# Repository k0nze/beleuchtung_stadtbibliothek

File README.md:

# Beleuchtung der LEGO Stadtbibliothek Stuttgart

## Platine
KiCad Projekt:
[beleuchtung_stadtbibliothek.pro](./kicad/beleuchtung_stadtbibliothek.pro)

Pin-Belegung `CON1`:

 * 1 => `VCC`
 * 2 => `GND`
 * 3 => `CLK`
 * 4 => Clear für für Schieberegister
 * 5 => Data-Input für Schieberegister 
 * 6 => Enable für LED-Treiber 

### Schaltplan
[beleuchtung_stadtbibliothek.sch](./kicad/beleuchtung_stadtbibliothek.sch)

### Layout/PCB
[beleuchtung_stadtbibliothek.kicad_pcb](./kicad/beleuchtung_stadtbibliothek.kicad_pcb)

### Gerber Dateien für Seeedstudio
[kicad/gerber](./kicad/gerber)

### Bauelemente (für 10 Platinen)
Reichelt:

 * 10x [Stiftleisten 2,54 mm, 2X03, gewinkelt](https://www.reichelt.de/Stiftleisten/MPE-088-2-006/3/index.html?ACTION=3&LA=2&ARTICLE=119904&GROUPID=7434&artnr=MPE+088-2-006&SEARCH=%252A)
 * 15x [50pol. Stiftleiste, gewinkelt, RM 2,54](https://www.reichelt.de/Stiftleisten/SL-1X50W-2-54/3/index.html?ACTION=3&LA=2&ARTICLE=19509&GROUPID=7434&artnr=SL+1X50W+2%2C54&SEARCH=%252A)
 * 50x [SMD HC 164](https://www.reichelt.de/ICs-74HC-SMD/SMD-HC-164/3/index.html?ACTION=3&LA=2&ARTICLE=18650&GROUPID=2931&artnr=SMD+HC+164&SEARCH=%252A)
 * 50x [SMD HC 244](https://www.reichelt.de/ICs-74HC-SMD/SMD-HC-244/3/index.html?ACTION=3&LA=2&ARTICLE=18663&GROUPID=2931&artnr=SMD+HC+244&SEARCH=%252A)
 * 2x [CR 44](https://www.reichelt.de/Flussmittel-Loetpasten/CR-44/3/index.html?ACTION=3&LA=2&ARTICLE=6833&GROUPID=4132&artnr=CR+44&SEARCH=%252A)
 * (3-5)x [GS25E05-P1J](https://www.reichelt.de/Festspannungsnetzteile/GS25E05-P1J/3/index.html?ACTION=3&LA=2&ARTICLE=161618&GROUPID=4946&artnr=GS25E05-P1J&SEARCH=%252A)
 * (3-5)x [DELOCK 65524](https://www.reichelt.de/Hohlstecker/DELOCK-65524/3/index.html?ACTION=3&LA=2&ARTICLE=143219&GROUPID=7488&artnr=DELOCK+65524&SEARCH=%252A)
 * 1x [EL 6-FACH MS-LG](https://www.reichelt.de/Steckdosenleiste-allgemein/EL-6-FACH-MS-LG/3/index.html?ACTION=3&LA=446&ARTICLE=34994&GROUPID=4280&artnr=EL+6-FACH+MS-LG&SEARCH=mehrfachsteckdose)
 * 360x [1/4W 5%](https://www.reichelt.de/1-4W-5-/2/index.html?ACTION=2&LA=2&GROUPID=3061)

eBay:

 * 500x [3mm LED weiß](http://www.ebay.de/itm/Transparente-High-Quality-LEDs-Leucht-Dioden-in-verschiedenen-Grosen-und-Farben-/171370401875?var=&hash=item27e678d053:m:myDHtgaZcdvr4vHanhSXiCA)
 * 18x [20cm Dupont Draht 40x](http://www.ebay.de/itm/40x-Dupont-Draht-Rainbow-Color-Jumper-Kabel-Buchse-Buchse-20cm-/351673233241?hash=item51e15baf59:g:O0cAAOxyaTxTRRo8)

Bricklink:

 * 360x [4070, white](https://www.bricklink.com/v2/catalog/catalogitem.page?P=4070#T=S&C=1&O={"color":1})

## Steuerung
Die Steuerung wird derzeit durch einen Arduino Mega 2560 übernommen. Der Anschluss der Steuerleitungen für die Platinen ist in [demo0.ino](./src/demo0/demo0.ino) dokumentiert. In [demo0.ino](./src/demo0/demo0.ino) werden alle LEDs eingeschaltet.

### Verdrahtung

* `VCC`: orange
* `GND`: blau/schwarz
* `CLK`: violett/orange
* reset: weiß
* data: gelb/grün
* driver: grau/braun

### Fertiges Modell

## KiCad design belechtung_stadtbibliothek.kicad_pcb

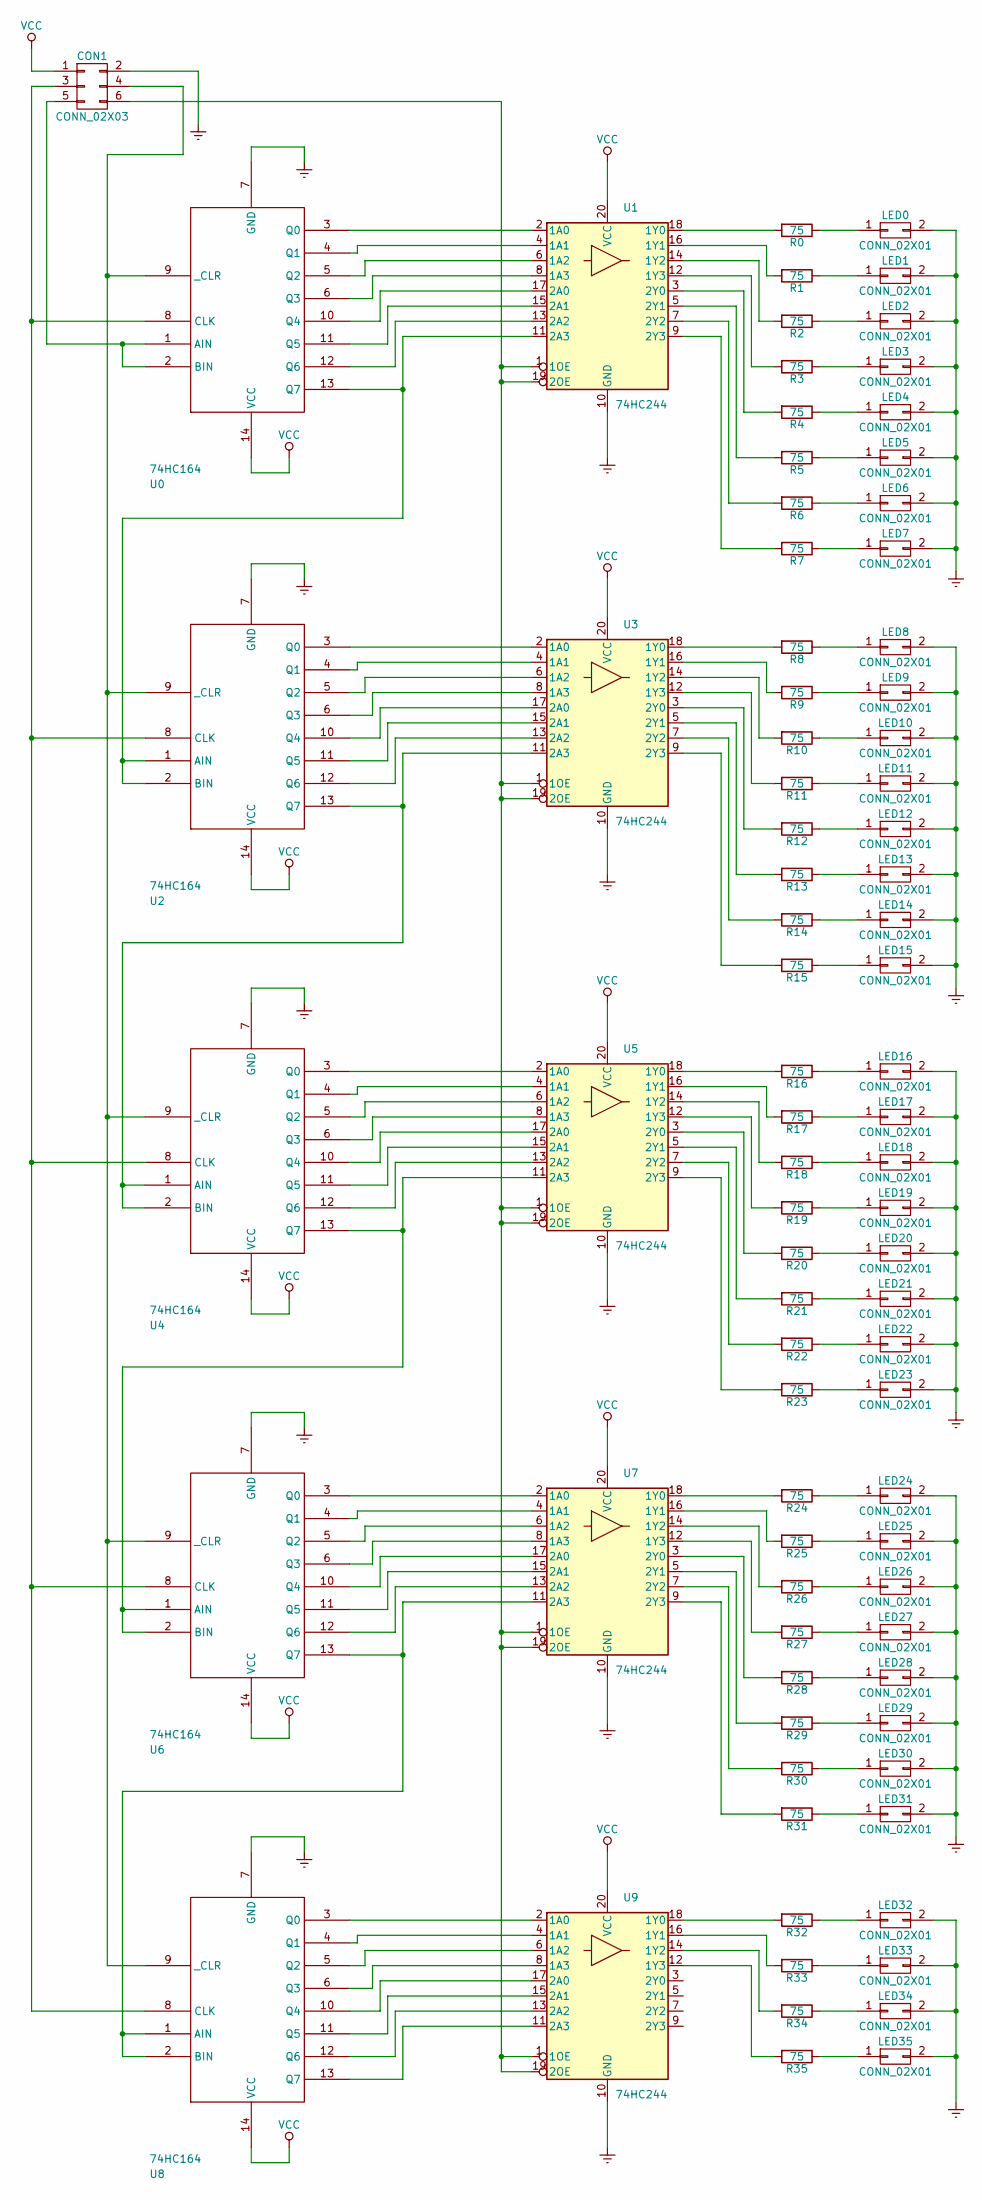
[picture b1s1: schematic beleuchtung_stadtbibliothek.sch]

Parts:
CON1: CONN_02X03; Pin_Header_Straight_2x03_Pitch2.54mm
LED0, LED1, LED2, LED3, LED4, LED5, LED6, LED7, LED8, LED9, LED10, LED11, LED12, LED13, LED14, LED15, LED16, LED17, LED18, LED19, LED20, LED21, LED22, LED23, LED24, LED25, LED26, LED27, LED28, LED29, LED30, LED31, LED32, LED33, LED34, LED35: CONN_02X01; Pin_Header_Angled_1x02_Pitch2.54mm
R0, R1, R2, R3, R4, R5, R6, R7, R8, R9, R10, R11, R12, R13, R14, R15, R16, R17, R18, R19, R20, R21, R22, R23, R24, R25, R26, R27, R28, R29, R30, R31, R32, R33, R34, R35: 75; R_Axial_DIN0204_L3.6mm_D1.6mm_P2.54mm_Vertical
U0, U2, U4, U6, U8: 74HC164; DIP-14_W7.62mm_LongPads
U1, U3, U5, U7, U9: 74HC244; DIP-20_W7.62mm_LongPads

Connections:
Earth: CON1.2, LED0.2, LED1.2, LED2.2, LED3.2, LED4.2, LED5.2, LED6.2, LED7.2, LED8.2, LED9.2, LED10.2, LED11.2, LED12.2, LED13.2, LED14.2, LED15.2, LED16.2, LED17.2, LED18.2, LED19.2, LED20.2, LED21.2, LED22.2, LED23.2, LED24.2, LED25.2, LED26.2, LED27.2, LED28.2, LED29.2, LED30.2, LED31.2, LED32.2, LED33.2, LED34.2, LED35.2, U0.7 (GND), U1.10 (GND), U2.7 (GND), U3.10 (GND), U4.7 (GND), U5.10 (GND), U6.7 (GND), U7.10 (GND), U8.7 (GND), U9.10 (GND)
unnamed: CON1.3, U0.8 (CLK), U2.8 (CLK), U4.8 (CLK), U6.8 (CLK), U8.8 (CLK)
unnamed: CON1.4, U0.9 (_CLR), U2.9 (_CLR), U4.9 (_CLR), U6.9 (_CLR), U8.9 (_CLR)
unnamed: CON1.5, U0.1 (AIN), U0.2 (BIN)
unnamed: CON1.6, U1.1 (1OE), U1.19 (2OE), U3.1 (1OE), U3.19 (2OE), U5.1 (1OE), U5.19 (2OE), U7.1 (1OE), U7.19 (2OE), U9.1 (1OE), U9.19 (2OE)
unnamed: LED0.1, R0.1
unnamed: LED1.1, R1.1
unnamed: LED2.1, R2.1
unnamed: LED3.1, R3.1
unnamed: LED4.1, R4.1
unnamed: LED5.1, R5.1
unnamed: LED6.1, R6.1
unnamed: LED7.1, R7.1
unnamed: LED8.1, R8.1
unnamed: LED9.1, R9.1
unnamed: LED10.1, R10.1
unnamed: LED11.1, R11.1
unnamed: LED12.1, R12.1
unnamed: LED13.1, R13.1
unnamed: LED14.1, R14.1
unnamed: LED15.1, R15.1
unnamed: LED16.1, R16.1
unnamed: LED17.1, R17.1
unnamed: LED18.1, R18.1
unnamed: LED19.1, R19.1
unnamed: LED20.1, R20.1
unnamed: LED21.1, R21.1
unnamed: LED22.1, R22.1
unnamed: LED23.1, R23.1
unnamed: LED24.1, R24.1
unnamed: LED25.1, R25.1
unnamed: LED26.1, R26.1
unnamed: LED27.1, R27.1
unnamed: LED28.1, R28.1
unnamed: LED29.1, R29.1
unnamed: LED30.1, R30.1
unnamed: LED31.1, R31.1
unnamed: LED32.1, R32.1
unnamed: LED33.1, R33.1
unnamed: LED34.1, R34.1
unnamed: LED35.1, R35.1
unnamed: R0.2, U1.18 (1Y0)
unnamed: R1.2, U1.16 (1Y1)
unnamed: R2.2, U1.14 (1Y2)
unnamed: R3.2, U1.12 (1Y3)
unnamed: R4.2, U1.3 (2Y0)
unnamed: R5.2, U1.5 (2Y1)
unnamed: R6.2, U1.7 (2Y2)
unnamed: R7.2, U1.9 (2Y3)
unnamed: R8.2, U3.18 (1Y0)
unnamed: R9.2, U3.16 (1Y1)
unnamed: R10.2, U3.14 (1Y2)
unnamed: R11.2, U3.12 (1Y3)
unnamed: R12.2, U3.3 (2Y0)
unnamed: R13.2, U3.5 (2Y1)
unnamed: R14.2, U3.7 (2Y2)
unnamed: R15.2, U3.9 (2Y3)
unnamed: R16.2, U5.18 (1Y0)
unnamed: R17.2, U5.16 (1Y1)
unnamed: R18.2, U5.14 (1Y2)
unnamed: R19.2, U5.12 (1Y3)
unnamed: R20.2, U5.3 (2Y0)
unnamed: R21.2, U5.5 (2Y1)
unnamed: R22.2, U5.7 (2Y2)
unnamed: R23.2, U5.9 (2Y3)
unnamed: R24.2, U7.18 (1Y0)
unnamed: R25.2, U7.16 (1Y1)
unnamed: R26.2, U7.14 (1Y2)
unnamed: R27.2, U7.12 (1Y3)
unnamed: R28.2, U7.3 (2Y0)
unnamed: R29.2, U7.5 (2Y1)
unnamed: R30.2, U7.7 (2Y2)
unnamed: R31.2, U7.9 (2Y3)
unnamed: R32.2, U9.18 (1Y0)
unnamed: R33.2, U9.16 (1Y1)
unnamed: R34.2, U9.14 (1Y2)
unnamed: R35.2, U9.12 (1Y3)
unnamed: U0.3 (Q0), U1.2 (1A0)
unnamed: U0.4 (Q1), U1.4 (1A1)
unnamed: U0.5 (Q2), U1.6 (1A2)
unnamed: U0.6 (Q3), U1.8 (1A3)
unnamed: U0.10 (Q4), U1.17 (2A0)
unnamed: U0.11 (Q5), U1.15 (2A1)
unnamed: U0.12 (Q6), U1.13 (2A2)
unnamed: U0.13 (Q7), U1.11 (2A3), U2.1 (AIN), U2.2 (BIN)
unnamed: U2.3 (Q0), U3.2 (1A0)
unnamed: U2.4 (Q1), U3.4 (1A1)
unnamed: U2.5 (Q2), U3.6 (1A2)
unnamed: U2.6 (Q3), U3.8 (1A3)
unnamed: U2.10 (Q4), U3.17 (2A0)
unnamed: U2.11 (Q5), U3.15 (2A1)
unnamed: U2.12 (Q6), U3.13 (2A2)
unnamed: U2.13 (Q7), U3.11 (2A3), U4.1 (AIN), U4.2 (BIN)
unnamed: U4.3 (Q0), U5.2 (1A0)
unnamed: U4.4 (Q1), U5.4 (1A1)
unnamed: U4.5 (Q2), U5.6 (1A2)
unnamed: U4.6 (Q3), U5.8 (1A3)
unnamed: U4.10 (Q4), U5.17 (2A0)
unnamed: U4.11 (Q5), U5.15 (2A1)
unnamed: U4.12 (Q6), U5.13 (2A2)
unnamed: U4.13 (Q7), U5.11 (2A3), U6.1 (AIN), U6.2 (BIN)
unnamed: U6.3 (Q0), U7.2 (1A0)
unnamed: U6.4 (Q1), U7.4 (1A1)
unnamed: U6.5 (Q2), U7.6 (1A2)
unnamed: U6.6 (Q3), U7.8 (1A3)
unnamed: U6.10 (Q4), U7.17 (2A0)
unnamed: U6.11 (Q5), U7.15 (2A1)
unnamed: U6.12 (Q6), U7.13 (2A2)
unnamed: U6.13 (Q7), U7.11 (2A3), U8.1 (AIN), U8.2 (BIN)
unnamed: U8.3 (Q0), U9.2 (1A0)
unnamed: U8.4 (Q1), U9.4 (1A1)
unnamed: U8.5 (Q2), U9.6 (1A2)
unnamed: U8.6 (Q3), U9.8 (1A3)
unnamed: U8.10 (Q4), U9.17 (2A0)
unnamed: U8.11 (Q5), U9.15 (2A1)
unnamed: U8.12 (Q6), U9.13 (2A2)
unnamed: U8.13 (Q7), U9.11 (2A3)
VCC: CON1.1, U0.14 (VCC), U1.20 (VCC), U2.14 (VCC), U3.20 (VCC), U4.14 (VCC), U5.20 (VCC), U6.14 (VCC), U7.20 (VCC), U8.14 (VCC), U9.20 (VCC)

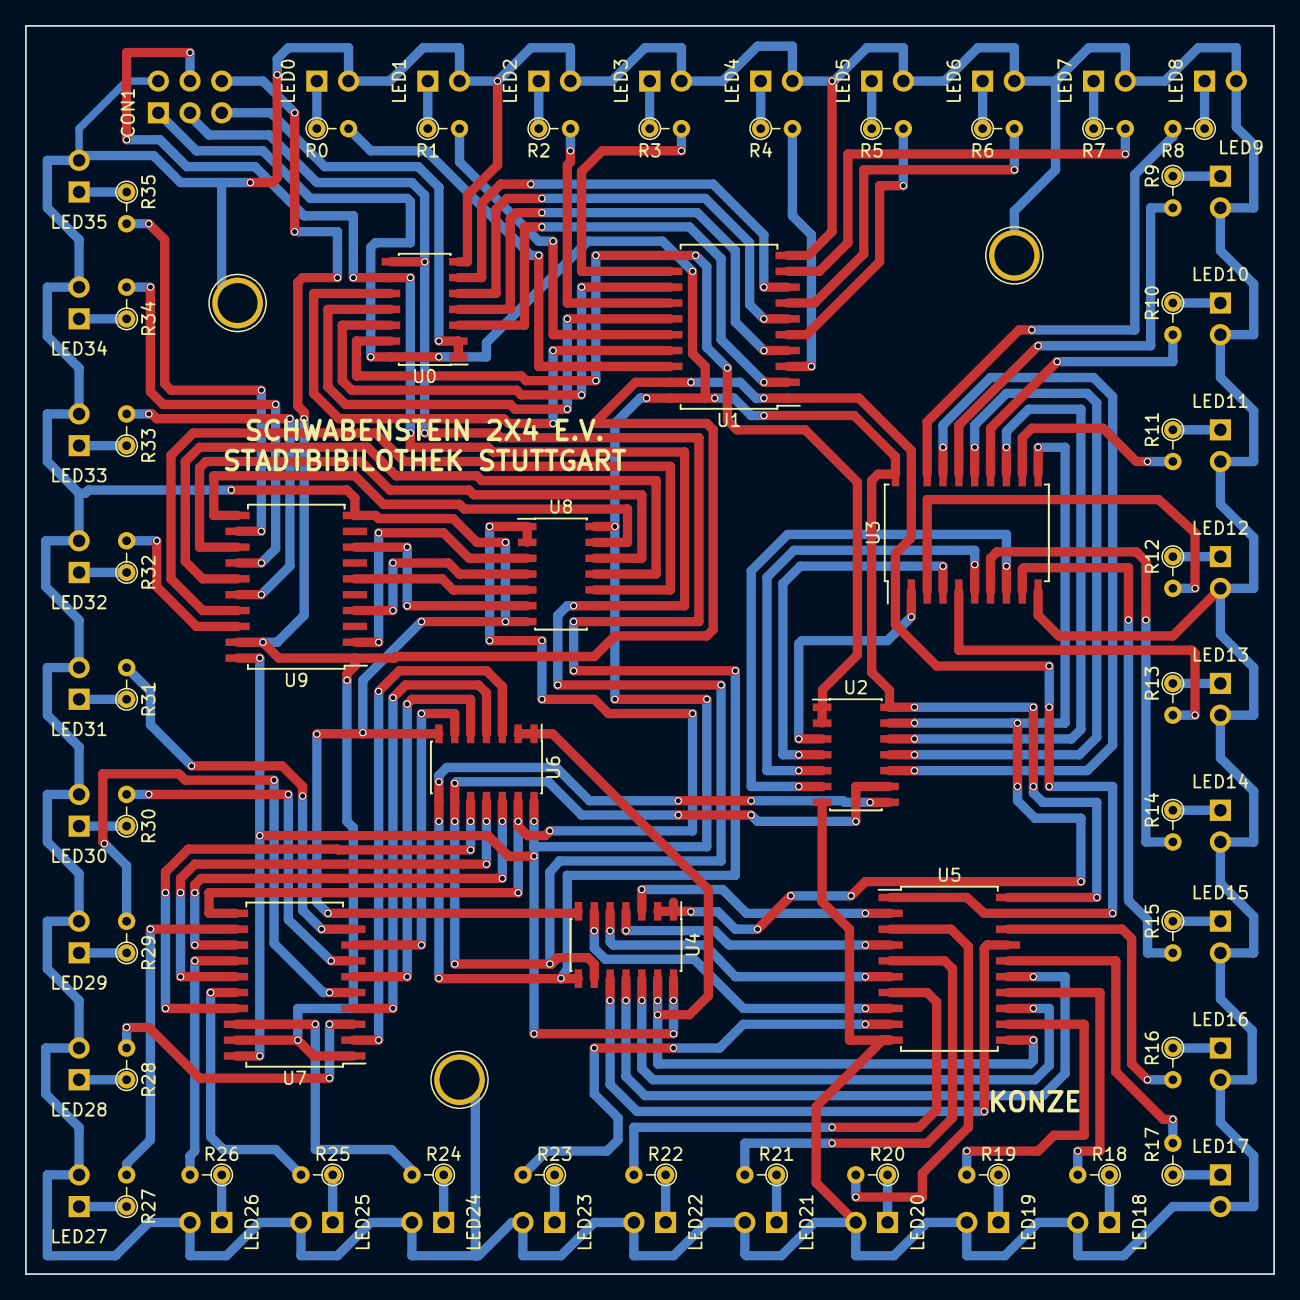
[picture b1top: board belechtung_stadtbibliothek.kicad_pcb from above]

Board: 2 copper layers, 100.0 x 100.0 mm, 83 parts (0 on the bottom side), 118 nets.

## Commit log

2017-06-18 Erster Commit.
2017-06-18 KiCad Dateien hinzugefügt.
2017-06-18 Dateien umbenannt.
2017-06-18 Dateien organisiert.
2017-06-18 fp-lib-table hinzugefügt.
2017-06-18 Materialliste eingetragen.
2017-06-23 Gerber Dateien für Seeedstudio hinzugefügt und Skript zum setzten der Dateinamen und packen als zip.
2017-11-01 Programm zum Testen der Platinen hinzugefügt.
2017-11-28 Verdrahtung und Demoprogramm hinzugefügt.
